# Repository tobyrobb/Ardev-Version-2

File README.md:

Ardev-Version-2
===============

A code repository for the ARDEV version 2 Arduino IDE based development board

Try here for information about the board.

http://tobyrobb.com/wordpress/?p=747

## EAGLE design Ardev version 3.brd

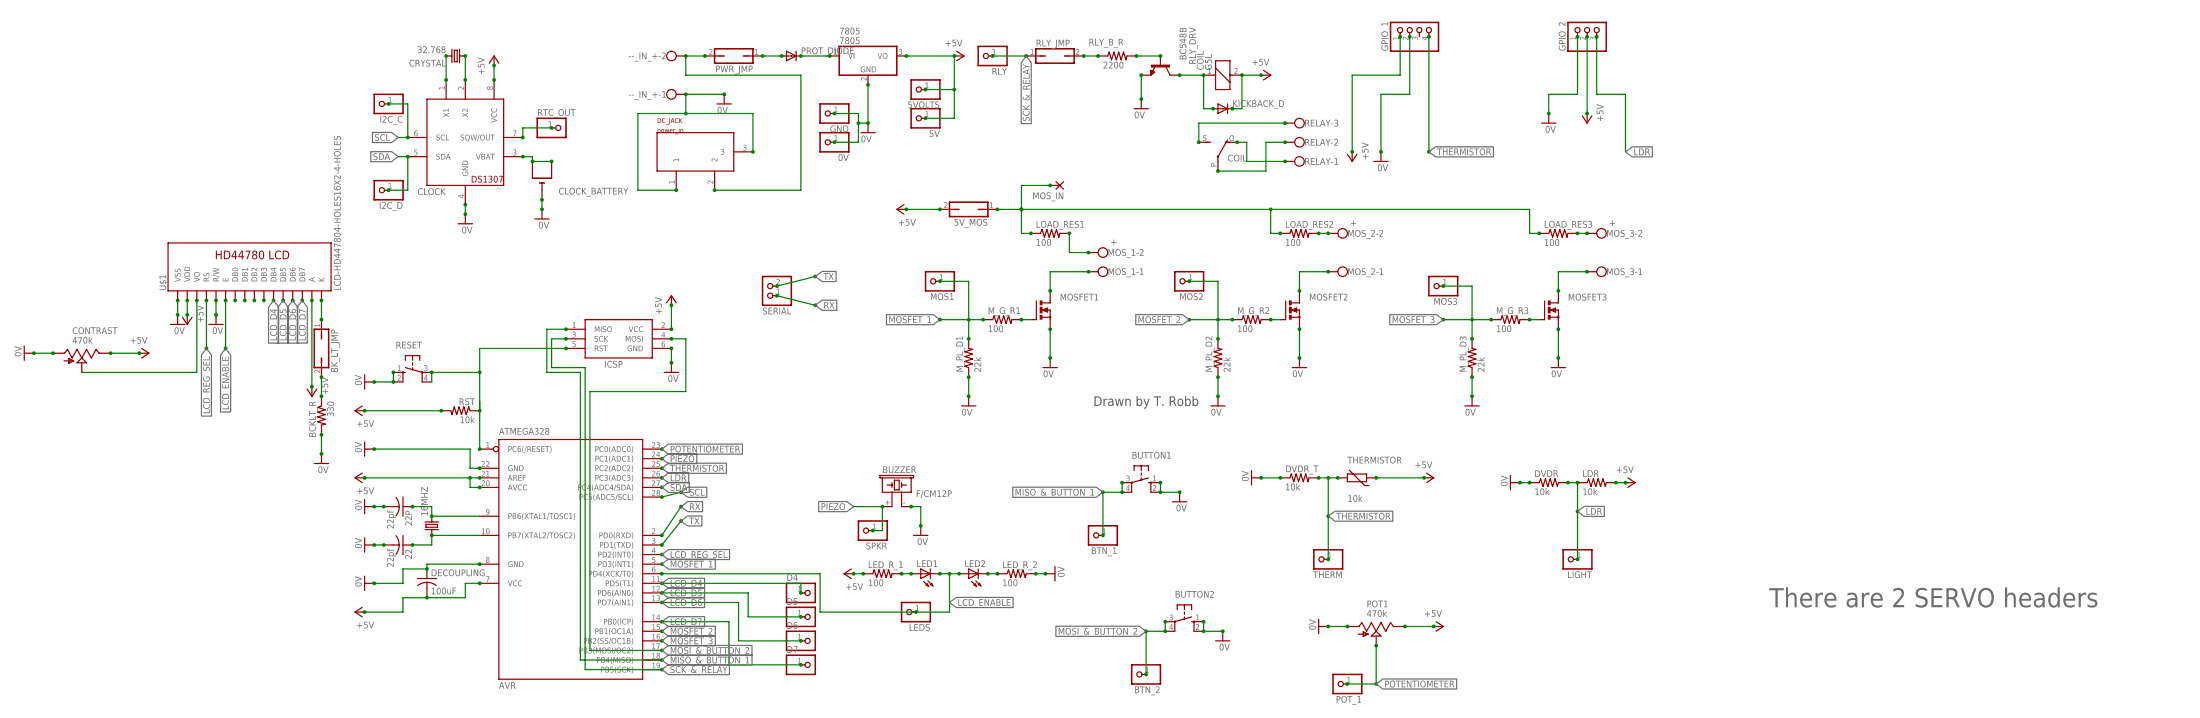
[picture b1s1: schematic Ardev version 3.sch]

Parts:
0V, 5V, 5VOLTS: PINHD-1X1; 1X01
5V_MOS: JP1Q; JP1
16MHZ: CRYSTALHC49U-V; HC49U-V
22, 22P: 22pf; C025-050X050
7805: 7805; TO220V
--_IN_+: W237-102
AVR: ATMEGA328; DIL28-3
BCKLT_R: 330; 0309V
BK_LT_JMP: JP1Q; JP1
BTN_1, BTN_2: PINHD-1X1; 1X01
BUTTON1, BUTTON2: 10-XX; B3F-10XX
BUZZER: F/CM12P
CLOCK: DS1307; DIL08
CLOCK_BATTERY: CR1220THM; CR1220-THM
COIL: G5L; G5LE
CONTRAST: 470k; CA6V
CRYSTAL: 32.768; TC26H
D4, D5, D6, D7: PINHD-1X1; 1X01
DC_JACK: power_in; SMARTPRJ_POWERSUPPLY_DC-21MM
DECOUPLING: 100uF; C025-050X050
DVDR: 10k; 0309V
DVDR_T: 10k; 0309V
GND: PINHD-1X1; 1X01
GPIO_1: PINHD-1X4; 1X04
GPIO_2: PINHD-1X3; 1X03
I2C_C, I2C_D: PINHD-1X1; 1X01
ICSP: AVRISP-6; AVRISP
KICKBACK_D: DIODE-D-7.5; D-7.5
LDR: 10k; 0309V
LED1, LED2: LED5MM
LEDS: PINHD-1X1; 1X01
LED_R_1, LED_R_2: 100; 0207/2V
LIGHT: PINHD-1X1; 1X01
LOAD_RES1, LOAD_RES2, LOAD_RES3: 100; 0309V
MOS1, MOS2, MOS3: PINHD-1X1; 1X01
MOSFET1, MOSFET2, MOSFET3: IRF512; TO220BV
MOS_1, MOS_2, MOS_3: +; W237-102
MOS_IN: 3,17/1,3
M_G_R1, M_G_R2, M_G_R3: 100; 0309V
M_PL_D1, M_PL_D2, M_PL_D3: 22k; 0309V
POT1: 470k; CA6V
POT_1: PINHD-1X1; 1X01
PROT_DIODE: DIODE-D-7.5; D-7.5
PWR_JMP: JP1Q; JP1
RELAY: W237-103
RESET: 10-XX; B3F-10XX
RLY: PINHD-1X1; 1X01
RLY_B_R: 2200; 0309V
RLY_DRV: BC548B; TO92-EBC
RLY_JMP: JP1Q; JP1
RST: 10k; 0309V
RTC_OUT: PINHD-1X1; 1X01
SERIAL: PINHD-1X2; 1X02
SPKR: PINHD-1X1; 1X01
THERM: PINHD-1X1; 1X01
THERMISTOR: 10k; RS-2,5
U$1: LCD-HD447804-HOLES16X2-4-HOLES; LCD-16X2-4HOLES

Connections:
0V: 0V.1, 22.2, 22P.2, 7805.2 (GND), --_IN_+.1, AVR.8 (GND), AVR.22 (GND), BCKLT_R.2, BUTTON1.1 (S), BUTTON1.2 (S1), BUTTON2.1 (S), BUTTON2.2 (S1), BUZZER.- (2), CLOCK.4 (GND), CLOCK_BATTERY.-, CONTRAST.A, DC_JACK.1, DC_JACK.3, DECOUPLING.1, DVDR.1, DVDR_T.1, GND.1, GPIO_1.2, GPIO_2.1, ICSP.6 (GND), LED_R_2.2, MOSFET1.S, MOSFET2.S, MOSFET3.S, M_PL_D1.1, M_PL_D2.1, M_PL_D3.1, POT1.A, RESET.1 (S), RESET.2 (S1), RLY_DRV.E, U$1.1 (VSS), U$1.5 (R/W)
+5V: 5V.1, 5VOLTS.1, 5V_MOS.2, 7805.3 (VO), AVR.7 (VCC), AVR.20 (AVCC), AVR.21 (AREF), CLOCK.8 (VCC), COIL.2, CONTRAST.E, DECOUPLING.2, GPIO_1.1, GPIO_2.2, ICSP.2 (VCC), KICKBACK_D.C, LDR.2, LED_R_1.1, POT1.E, RST.2, THERMISTOR.1, U$1.2 (VDD), U$1.15 (A)
LCD_D4: AVR.11 (PD5(T1)), D4.1, U$1.11 (DB4)
LCD_D5: AVR.12 (PD6(AIN0)), D5.1, U$1.12 (DB5)
LCD_D6: AVR.13 (PD7(AIN1)), D6.1, U$1.13 (DB6)
LCD_D7: AVR.14 (PB0(ICP)), D7.1, U$1.14 (DB7)
LCD_ENABLE: AVR.6 (PD4(XCK/T0)), LED1.K (C), LED2.A, LEDS.1, U$1.6 (E)
LCD_REG_SEL: AVR.4 (PD2(INT0)), U$1.4 (RS)
LDR: AVR.26 (PC3(ADC3)), DVDR.2, GPIO_2.3, LDR.1, LIGHT.1
MISO_&_BUTTON_1: AVR.18 (PB4(MISO)), BTN_1.1, BUTTON1.3, BUTTON1.4 (P1), ICSP.1 (MISO)
MOSFET_1: AVR.5 (PD3(INT1)), MOS1.1, M_G_R1.1, M_PL_D1.2
MOSFET_2: AVR.15 (PB1(OC1A)), MOS2.1, M_G_R2.1, M_PL_D2.2
MOSFET_3: AVR.16 (PB2(SS/OC1B)), MOS3.1, M_G_R3.1, M_PL_D3.2
MOSI_&_BUTTON_2: AVR.17 (PB3(MOSI/OC2)), BTN_2.1, BUTTON2.3, BUTTON2.4 (P1), ICSP.4 (MOSI)
unnamed: --_IN_+.2, DC_JACK.2, PWR_JMP.2
unnamed: PROT_DIODE.A, PWR_JMP.1
unnamed: AVR.1 (PC6(/RESET)), ICSP.5 (RST), RESET.3, RESET.4 (P1), RST.1
unnamed: 7805.1 (VI), PROT_DIODE.C
unnamed: LOAD_RES1.2, MOS_1.2
unnamed: MOSFET1.D, MOS_1.1
unnamed: 16MHZ.2, 22P.1, AVR.9 (PB6(XTAL1/TOSC1))
unnamed: LOAD_RES3.2, MOS_3.2
unnamed: MOSFET3.D, MOS_3.1
unnamed: 16MHZ.1, 22.1, AVR.10 (PB7(XTAL2/TOSC2))
unnamed: LOAD_RES2.2, MOS_2.2
unnamed: MOSFET2.D, MOS_2.1
unnamed: CLOCK.2 (X2), CRYSTAL.1
unnamed: CLOCK.1 (X1), CRYSTAL.2
unnamed: CLOCK.3 (VBAT), CLOCK_BATTERY.+1 (+), CLOCK_BATTERY.+2 (+1)
unnamed: LED1.A, LED_R_1.2
unnamed: COIL.O, RELAY.1
unnamed: COIL.P, RELAY.2
unnamed: COIL.S, RELAY.3
unnamed: 5V_MOS.1, LOAD_RES1.1, LOAD_RES2.1, LOAD_RES3.1, MOS_IN.1
unnamed: LED2.K (C), LED_R_2.1
unnamed: CLOCK.7 (SQW/OUT), RTC_OUT.1
unnamed: COIL.1, KICKBACK_D.A, RLY_DRV.C
unnamed: MOSFET3.G, M_G_R3.2
unnamed: CONTRAST.S, U$1.3 (VO)
unnamed: MOSFET2.G, M_G_R2.2
unnamed: MOSFET1.G, M_G_R1.2
unnamed: BK_LT_JMP.1, U$1.16 (K)
unnamed: BCKLT_R.1, BK_LT_JMP.2
unnamed: RLY_B_R.2, RLY_DRV.B
unnamed: RLY_B_R.1, RLY_JMP.2
PIEZO: AVR.24 (PC1(ADC1)), BUZZER.+ (1), SPKR.1
POTENTIOMETER: AVR.23 (PC0(ADC0)), POT1.S, POT_1.1
RX: AVR.2 (PD0(RXD)), SERIAL.1
SCK_&_RELAY: AVR.19 (PB5(SCK)), ICSP.3 (SCK), RLY.1, RLY_JMP.1
SCL: AVR.28 (PC5(ADC5/SCL)), CLOCK.6 (SCL), I2C_C.1
SDA: AVR.27 (PC4(ADC4/SDA)), CLOCK.5 (SDA), I2C_D.1
THERMISTOR: AVR.25 (PC2(ADC2)), DVDR_T.2, GPIO_1.4, THERM.1, THERMISTOR.2
TX: AVR.3 (PD1(TXD)), SERIAL.2

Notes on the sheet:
Drawn by T. Robb
There are 2 SERVO headers

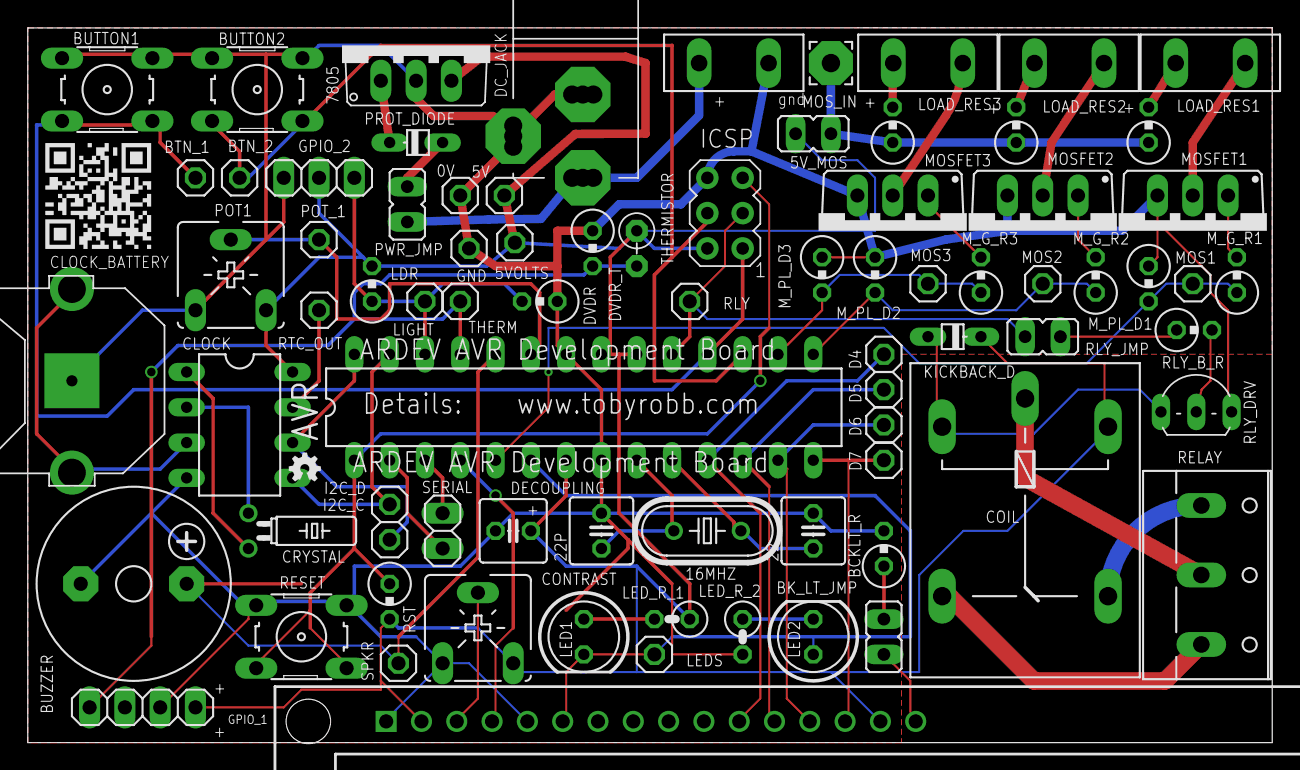
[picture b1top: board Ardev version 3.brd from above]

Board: 2 copper layers, 89.5 x 51.4 mm, 80 parts (0 on the bottom side), 53 nets.

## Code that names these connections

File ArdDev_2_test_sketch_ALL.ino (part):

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
LED / LCD  is the same pin, have only one or the other, is the LCD enable pin
RELAY is also the SCK pin *therefore may need to REMOVE relay jumper for programming
THERMISTOR / MOVEMENT SENSOR is the same pin, have only one or the other
LDR / SERVO  is the same pin, have only one or the other LOW turns on LCD

you must enable the internal pullups for the buttons by setting as inputs then writing HIGH
The leds if fitted also require the pullups to be enabled
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// Defines

#define ldrPin A3 // Light dependant resistor pin on board.
#define thermistorPin A2  //Temperature thermistor pin on board.
#define ledPin 4  // Led pin High for one colour Low for another
#define speakerPin A1  // The onboard speaker pin
#define relayPin 13 // Pin for the relay 
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#define dataPin A4  // The I2C bus DATA pin  
#define clockPin A5  // The I2C CLOCK pin

#define potPin A0 // Potentiometer on the board.

#define button1Pin 12  // Button 1 pin
#define button2Pin 11 // Button 2 pin
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  pinMode(ledPin, OUTPUT);  // You MUST use this if the LED's are fitted.
  pinMode(relayPin, OUTPUT);  //  If the relay is fitted.
  pinMode(speakerPin, OUTPUT);  // If the speaker is fitted.
  pinMode(potPin, INPUT);  // If the potentiometer is fitted
  pinMode(button1Pin, INPUT);  // If the button is fitted (write HIGH to enable pullups)
  pinMode(button2Pin, INPUT);  // If the button is fitted (write HIGH to enable pullups)
  pinMode(mosfet1Pin, OUTPUT);  // Mosfet 1 output
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
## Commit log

2014-05-04 Arduino development board ARDEV version 2
    A code repository for the ARDEV version 2 Arduino IDE based development
    board
2014-05-04 ARDEV2 Arduino development board examples
    ARDEV2 Arduino development board examples
2014-05-05 Arduino Development Board Version 2
    Arduino Development Board Version 2
2014-08-06 Create LEDWidget_wiggo_V3
